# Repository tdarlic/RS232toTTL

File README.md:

# TTL to RS232 adaptor

RS232 to TTL serial adaptor made for hand assembly based on 
http://www.uchobby.com/index.php/2007/06/11/ttl-to-rs232-adaptor-explained/

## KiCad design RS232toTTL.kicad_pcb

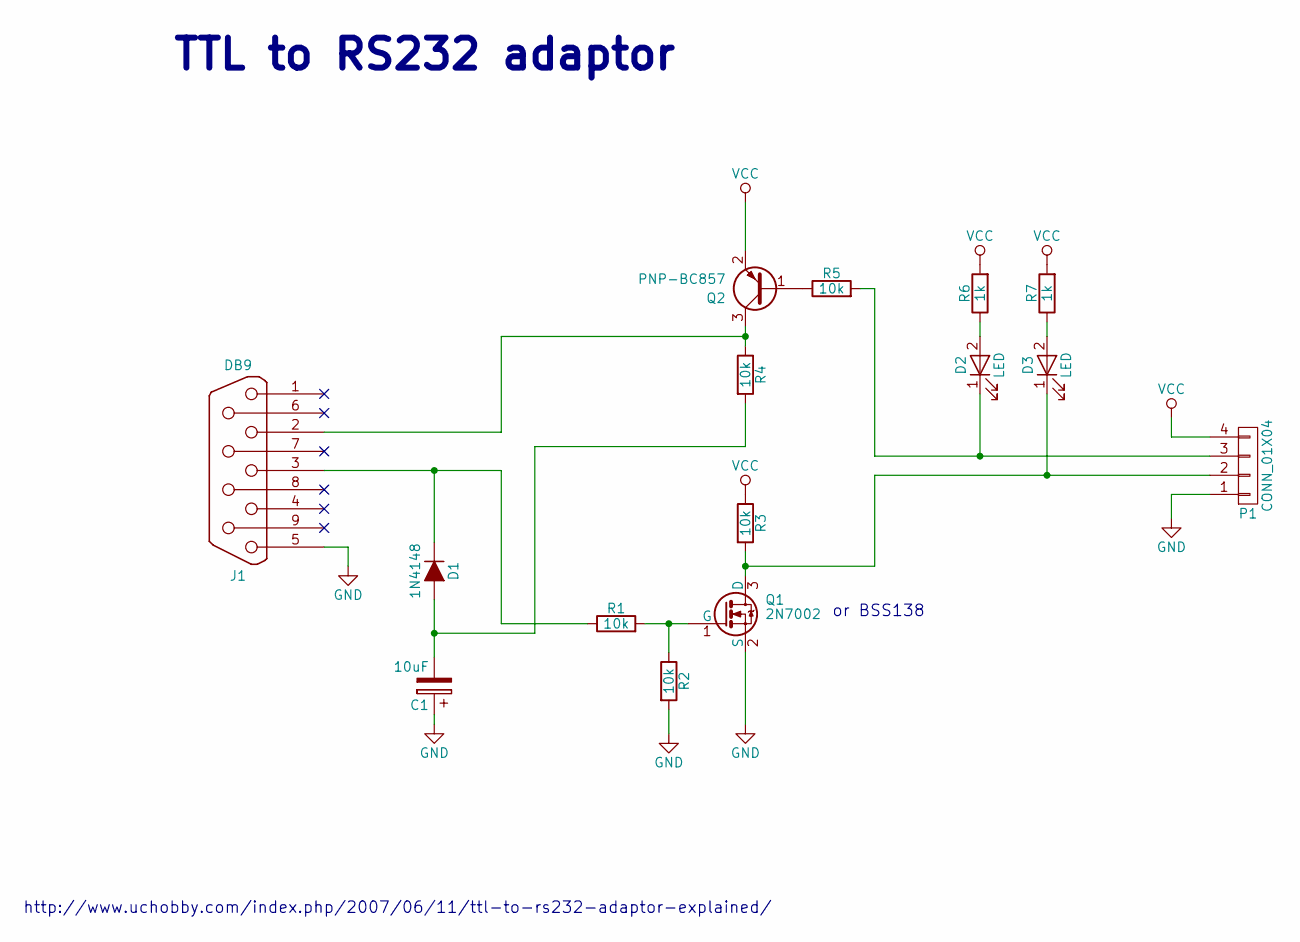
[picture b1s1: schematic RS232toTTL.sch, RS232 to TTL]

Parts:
C1: 10uF; c_elec_6.3x7.7
D1: 1N4148; MiniMELF_Handsoldering
D2, D3: LED; LED_0603
J1: DB9; DB9FC
P1: CONN_01X04; Pin_Header_Angled_1x04_Pitch2.54mm
Q1: 2N7002; SOT-23
Q2: PNP-BC857; SOT-23
R1, R2, R3, R4, R5: 10k; R_0603_HandSoldering
R6, R7: 1k; R_0603_HandSoldering

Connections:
GND: C1.1, J1.5, P1.1, Q1.2 (S), R2.2
unnamed: C1.2, D1.2 (A), R4.2
unnamed: D1.1 (K), J1.3, R1.1
unnamed: D2.1 (K), P1.3, R5.2
unnamed: D2.2 (A), R6.1
unnamed: D3.1 (K), P1.2, Q1.3 (D), R3.2
unnamed: D3.2 (A), R7.1
unnamed: J1.2, Q2.3 (C), R4.1
unnamed: Q1.1 (G), R1.2, R2.1
unnamed: Q2.1 (B), R5.1
VCC: P1.4, Q2.2 (E), R3.1, R6.2, R7.2

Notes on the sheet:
http://www.uchobby.com/index.php/2007/06/11/ttl-to-rs232-adaptor-explained/
TTL to RS232 adaptor
or BSS138

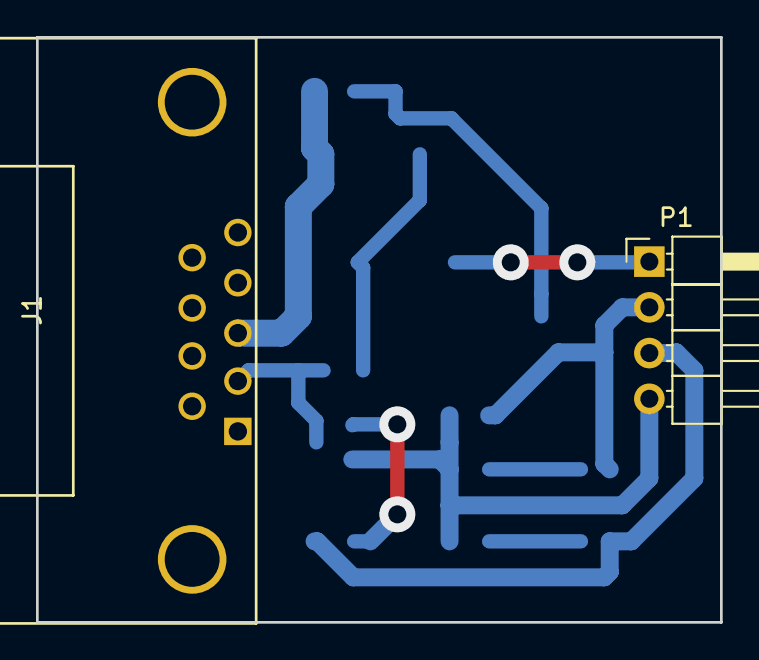
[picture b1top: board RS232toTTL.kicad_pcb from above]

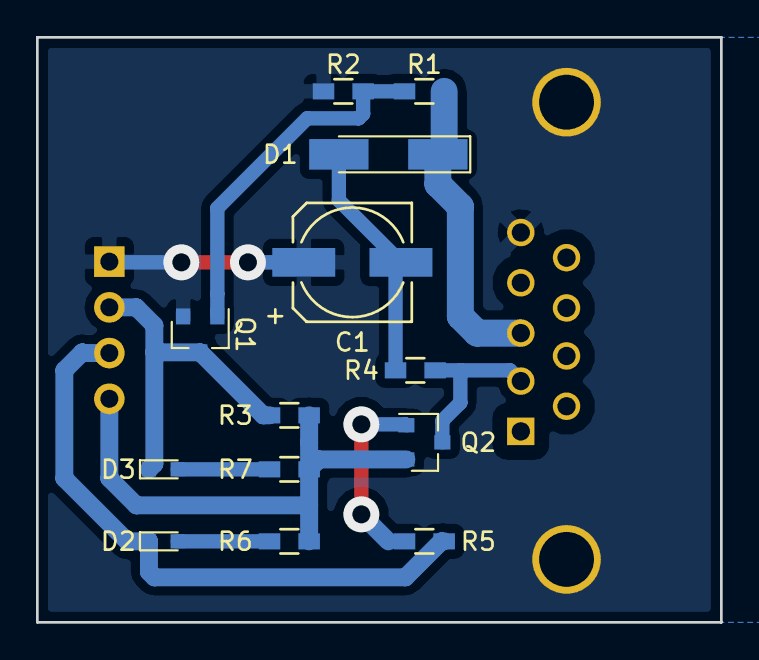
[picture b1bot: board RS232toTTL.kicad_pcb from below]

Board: 2 copper layers, 38.0 x 32.5 mm, 15 parts (13 on the bottom side), 11 nets.

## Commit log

2018-02-12 Editing readme
2018-02-12 Adding Kicad design files
2018-02-13 Routing PCB
2018-02-13 Finalizing the PCB, first print successful
2018-02-13 Adding PDF
